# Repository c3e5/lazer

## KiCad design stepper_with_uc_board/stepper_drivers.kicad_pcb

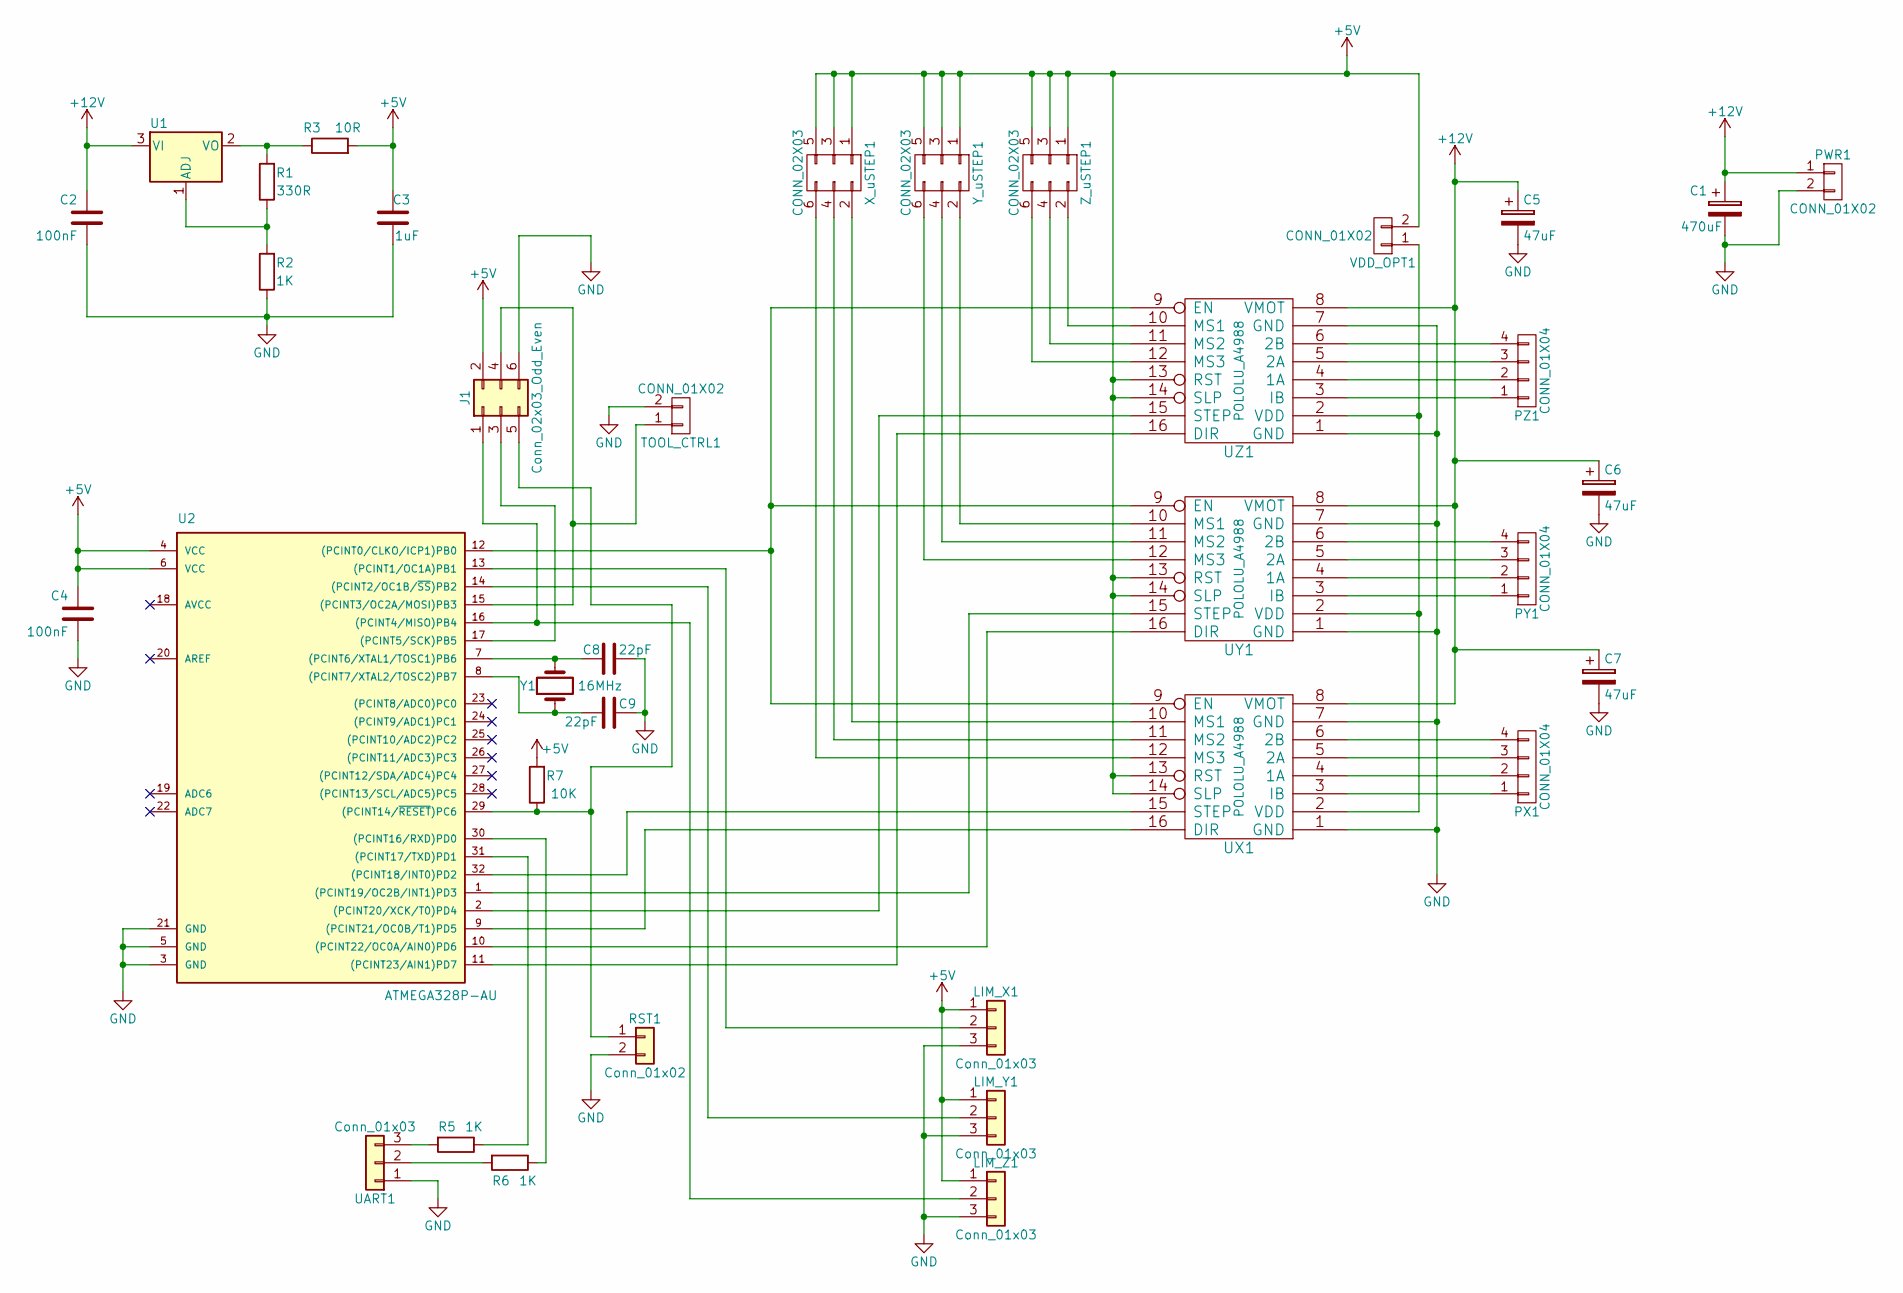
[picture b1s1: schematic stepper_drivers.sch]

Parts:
C1: 470uF; CP_Radial_D6.3mm_P2.50mm
C2, C4: 100nF; C_Rect_L4.0mm_W2.5mm_P2.50mm
C3: 1uF; CP_Radial_D4.0mm_P2.00mm
C5, C6, C7: 47uF; CP_Radial_D6.3mm_P2.50mm
C8, C9: 22pF; C_Rect_L4.0mm_W2.5mm_P2.50mm
J1: Conn_02x03_Odd_Even; Pin_Header_Straight_2x03_Pitch2.54mm
LIM_X1: Conn_01x03; Pin_Header_Straight_1x03_Pitch2.54mm
LIM_Y1: Conn_01x03; Pin_Header_Straight_1x03_Pitch2.54mm
LIM_Z1: Conn_01x03; Pin_Header_Straight_1x03_Pitch2.54mm
PWR1: CONN_01X02; TerminalBlock_Altech_AK300-2_P5.00mm
PX1: CONN_01X04; Socket_MOLEX-KK-RM2-54mm_Lock_4pin_straight
PY1: CONN_01X04; Socket_MOLEX-KK-RM2-54mm_Lock_4pin_straight
PZ1: CONN_01X04; Socket_MOLEX-KK-RM2-54mm_Lock_4pin_straight
R1: 330R; C_Rect_L4.0mm_W2.5mm_P2.50mm
R2, R5, R6: 1K; C_Rect_L4.0mm_W2.5mm_P2.50mm
R3: 10R; C_Rect_L4.0mm_W2.5mm_P2.50mm
R7: 10K; C_Rect_L4.0mm_W2.5mm_P2.50mm
RST1: Conn_01x02; TerminalBlock_bornier-2_P5.08mm
TOOL_CTRL1: CONN_01X02; Socket_MOLEX-KK-RM2-54mm_Lock_2pin_straight
U1: LM317_3PinPackage; SOT-223-3_TabPin2
U2: ATMEGA328P-AU; My_TQFP-32_7x7mm_Pitch0.8mm
UART1: Conn_01x03; Pin_Header_Straight_1x03_Pitch2.54mm
UX1: POLOLU_A4988; A4988
UY1: POLOLU_A4988; A4988
UZ1: POLOLU_A4988; A4988
VDD_OPT1: CONN_01X02; Pin_Header_Straight_1x02_Pitch2.54mm
X_uSTEP1: CONN_02X03; Pin_Header_Straight_2x03_Pitch2.54mm
Y1: 16MHz; Crystal_HC49-U_Vertical
Y_uSTEP1: CONN_02X03; Pin_Header_Straight_2x03_Pitch2.54mm
Z_uSTEP1: CONN_02X03; Pin_Header_Straight_2x03_Pitch2.54mm

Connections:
+5V: C3.2, C4.2, J1.2, LIM_X1.1, LIM_Y1.1, LIM_Z1.1, R3.2, R7.2, U2.4 (VCC), U2.6 (VCC), UX1.13 (RST), UX1.14 (SLP), UY1.13 (RST), UY1.14 (SLP), UZ1.13 (RST), UZ1.14 (SLP), VDD_OPT1.2, X_uSTEP1.1, X_uSTEP1.3, X_uSTEP1.5, Y_uSTEP1.1, Y_uSTEP1.3, Y_uSTEP1.5, Z_uSTEP1.1, Z_uSTEP1.3, Z_uSTEP1.5; also elsewhere on the board
+12V: C1.1, C2.2, C5.1, C6.1, C7.1, PWR1.1, U1.3 (VI), UX1.8 (VMOT), UY1.8 (VMOT), UZ1.8 (VMOT)
GND: C1.2, C2.1, C3.1, C4.1, C5.2, C6.2, C7.2, C8.1, C9.1, J1.6, LIM_X1.3, LIM_Y1.3, LIM_Z1.3, PWR1.2, R2.1, RST1.2, TOOL_CTRL1.2, U2.3 (GND), U2.5 (GND), U2.21 (GND), UART1.1, UX1.1 (GND), UX1.7 (GND), UY1.1 (GND), UY1.7 (GND), UZ1.1 (GND), UZ1.7 (GND); also elsewhere on the board
unnamed: C8.2, U2.7 ((PCINT6/XTAL1/TOSC1)PB6), Y1.2
unnamed: C9.2, U2.8 ((PCINT7/XTAL2/TOSC2)PB7), Y1.1
unnamed 5: J1.1, LIM_Z1.2, U2.16 ((PCINT4/MISO)PB4); also elsewhere on the board
unnamed 6: J1.3, U2.17 ((PCINT5/SCK)PB5); also elsewhere on the board
unnamed 7: J1.4, TOOL_CTRL1.1, U2.15 ((PCINT3/OC2A/MOSI)PB3); also elsewhere on the board
unnamed 8: J1.5, R7.1, RST1.1, U2.29 ((PCINT14/~RESET~)PC6); also elsewhere on the board
unnamed: LIM_X1.2, U2.13 ((PCINT1/OC1A)PB1)
unnamed 10: LIM_Y1.2, U2.14 ((PCINT2/OC1B/~SS~)PB2); also elsewhere on the board
unnamed: PX1.1, UX1.3 (IB)
unnamed: PX1.2, UX1.4 (1A)
unnamed: PX1.3, UX1.5 (2A)
unnamed: PX1.4, UX1.6 (2B)
unnamed: PY1.1, UY1.3 (IB)
unnamed: PY1.2, UY1.4 (1A)
unnamed: PY1.3, UY1.5 (2A)
unnamed: PY1.4, UY1.6 (2B)
unnamed: PZ1.1, UZ1.3 (IB)
unnamed: PZ1.2, UZ1.4 (1A)
unnamed: PZ1.3, UZ1.5 (2A)
unnamed: PZ1.4, UZ1.6 (2B)
unnamed: R1.1, R2.2, U1.1 (ADJ)
unnamed: R1.2, R3.1, U1.2 (VO)
unnamed: R5.1, U2.31 ((PCINT17/TXD)PD1)
unnamed: R5.2, UART1.3
unnamed: R6.1, U2.30 ((PCINT16/RXD)PD0)
unnamed: R6.2, UART1.2
unnamed: U2.1 ((PCINT19/OC2B/INT1)PD3), UY1.15 (STEP)
unnamed: U2.2 ((PCINT20/XCK/T0)PD4), UZ1.15 (STEP)
unnamed: U2.9 ((PCINT21/OC0B/T1)PD5), UX1.16 (DIR)
unnamed: U2.10 ((PCINT22/OC0A/AIN0)PD6), UY1.16 (DIR)
unnamed: U2.11 ((PCINT23/AIN1)PD7), UZ1.16 (DIR)
unnamed: U2.12 ((PCINT0/CLKO/ICP1)PB0), UX1.9 (EN), UY1.9 (EN), UZ1.9 (EN)
unnamed: U2.32 ((PCINT18/INT0)PD2), UX1.15 (STEP)
unnamed: UX1.2 (VDD), UY1.2 (VDD), UZ1.2 (VDD), VDD_OPT1.1
unnamed: UX1.10 (MS1), X_uSTEP1.2
unnamed: UX1.11 (MS2), X_uSTEP1.4
unnamed: UX1.12 (MS3), X_uSTEP1.6
unnamed: UY1.10 (MS1), Y_uSTEP1.2
unnamed: UY1.11 (MS2), Y_uSTEP1.4
unnamed: UY1.12 (MS3), Y_uSTEP1.6
unnamed: UZ1.10 (MS1), Z_uSTEP1.2
unnamed: UZ1.11 (MS2), Z_uSTEP1.4
unnamed: UZ1.12 (MS3), Z_uSTEP1.6

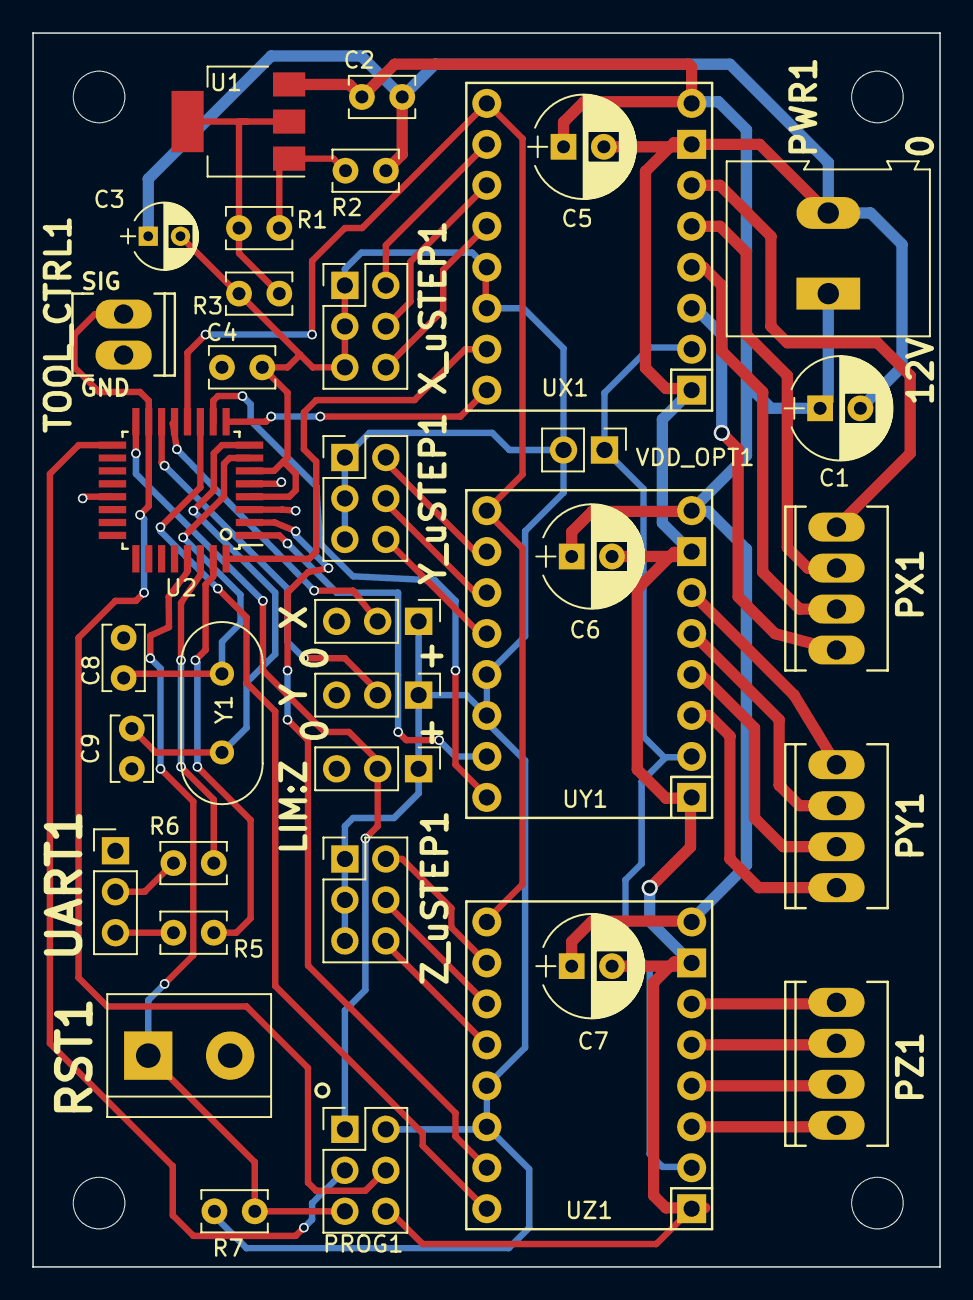
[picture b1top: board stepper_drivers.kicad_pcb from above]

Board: 2 copper layers, 56.2 x 76.5 mm, 36 parts (0 on the bottom side), 46 nets.

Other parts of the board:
LIM:Z   Y   X: Conn_01x03; Pin_Header_Straight_1x03_Pitch2.54mm
PROG1: Conn_02x03_Odd_Even; Pin_Header_Straight_2x03_Pitch2.54mm

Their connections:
+5V: LIM:Z Y X.1, PROG1.2; also elsewhere on the board
GND: LIM:Z Y X.3, PROG1.6; also elsewhere on the board
unnamed 5: PROG1.1; also elsewhere on the board
unnamed 6: PROG1.3; also elsewhere on the board
unnamed 7: PROG1.4; also elsewhere on the board
unnamed 8: PROG1.5; also elsewhere on the board
unnamed 10: LIM:Z Y X.2; also elsewhere on the board

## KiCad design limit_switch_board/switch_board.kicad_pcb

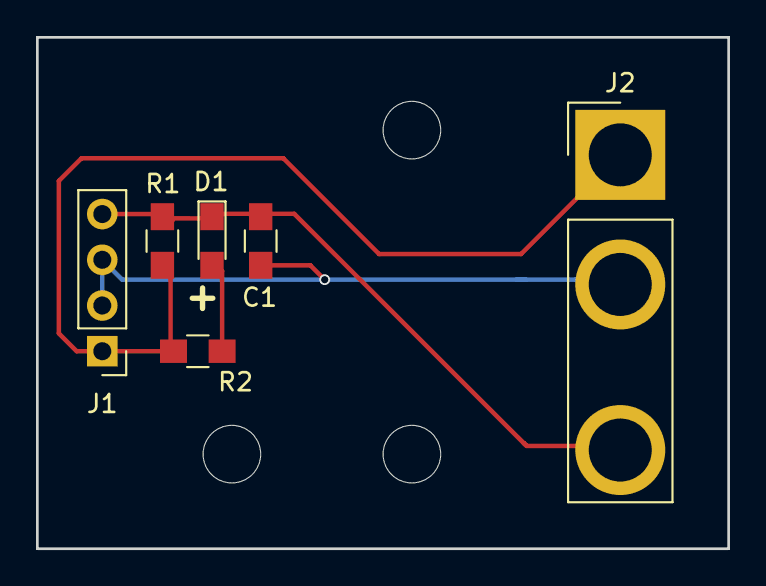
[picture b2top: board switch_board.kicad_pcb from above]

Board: 2 copper layers, 38.4 x 28.4 mm, 6 parts (0 on the bottom side), 4 nets.

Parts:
C1: 100nF; R_0805_HandSoldering
D1: LED; LED_0805_HandSoldering
J1: CONN_01X04; Pin_Header_Straight_1x04_Pitch2.54mm
J2: CONN_01X03; limit_switch_bomba
R1: 10K; R_0805_HandSoldering
R2: 1K; R_0805_HandSoldering

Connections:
+5V: J1.1, J2.2, R1.1, R2.1
GND: C1.2, J1.2, J1.3, J2.3
unnamed: C1.1, D1.1, J1.4, J2.1, R1.2
unnamed: D1.2, R2.2

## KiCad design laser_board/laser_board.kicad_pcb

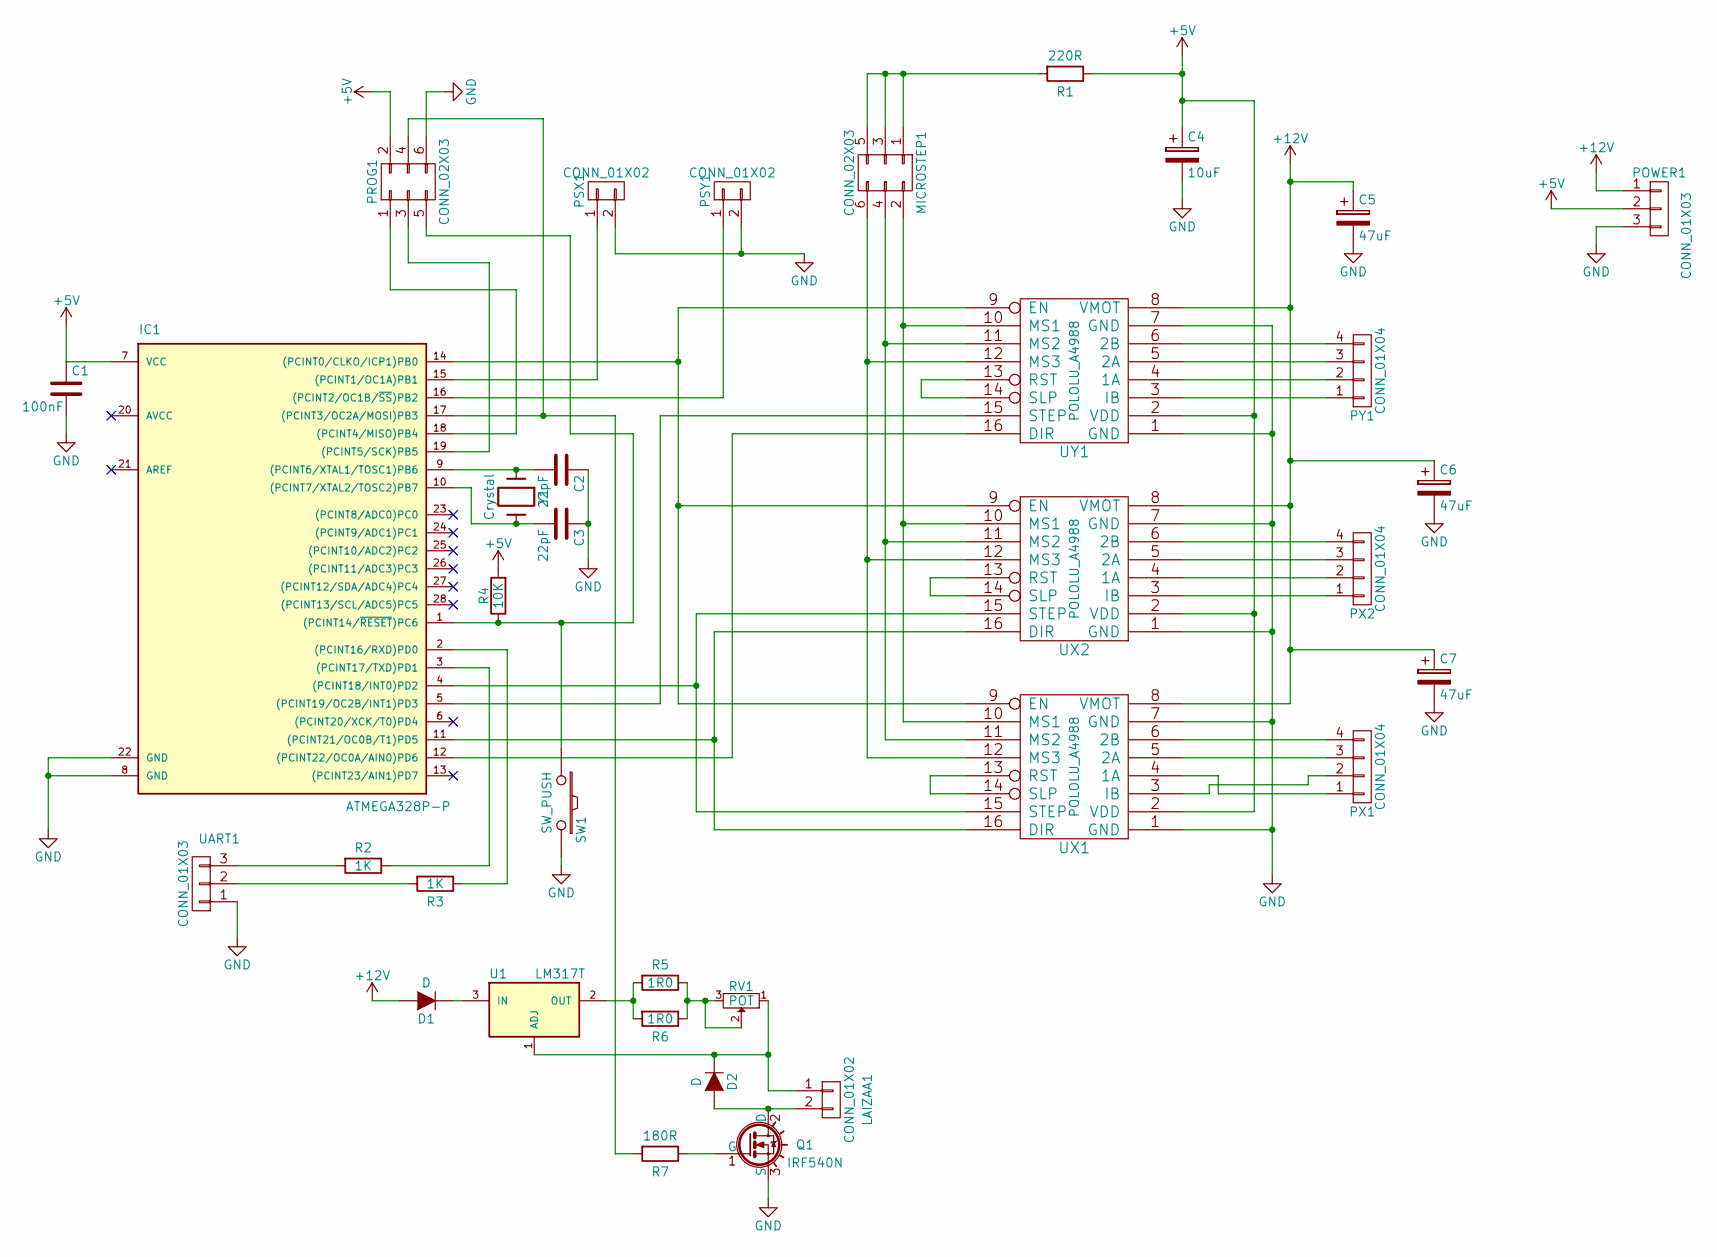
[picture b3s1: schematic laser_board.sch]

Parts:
C1: 100nF; C_Rect_L4_W2.5_P2.5
C2, C3: 22pF; C_Rect_L4_W2.5_P2.5
C4: 10uF; C_Radial_D5_L11_P2.5
C5, C6, C7: 47uF; C_Radial_D6.3_L11.2_P2.5
D1, D2: D; Diode_DO-41_SOD81_Vertical_KathodeUp
IC1: ATMEGA328P-P; DIP-28_W7.62mm
LAIZAA1: CONN_01X02; Socket_MOLEX-KK-RM2-54mm_Lock_2pin_straight
MICROSTEP1: CONN_02X03; Pin_Header_Straight_2x03
POWER1: CONN_01X03; Socket_MOLEX-KK-RM2-54mm_Lock_3pin_straight
PROG1: CONN_02X03; Pin_Header_Straight_2x03
PSX1: CONN_01X02; Socket_MOLEX-KK-RM2-54mm_Lock_2pin_straight
PSY1: CONN_01X02; Socket_MOLEX-KK-RM2-54mm_Lock_2pin_straight
PX1, PX2: CONN_01X04; Socket_MOLEX-KK-RM2-54mm_Lock_4pin_straight
PY1: CONN_01X04; Socket_MOLEX-KK-RM2-54mm_Lock_4pin_straight
Q1: IRF540N; TO-220
R1: 220R; C_Rect_L4_W2.5_P2.5
R2, R3: 1K; C_Rect_L4_W2.5_P2.5
R4: 10K; C_Rect_L4_W2.5_P2.5
R5, R6: 1R0; Resistor_Vertical_RM5mm
R7: 180R; C_Rect_L4_W2.5_P2.5
RV1: POT; Potentiometer_Bourns_3006P_Angular_ScrewFront
SW1: SW_PUSH; SIMPLE_SWITCH
U1: LM317T; TO-220
UART1: CONN_01X03; Pin_Header_Straight_1x03
UX1, UX2: POLOLU_A4988; A4988
UY1: POLOLU_A4988; A4988
Y1: Crystal; Crystal_HC49-U_Vertical

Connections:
+5V: C1.1, C4.1, IC1.7 (VCC), POWER1.2, PROG1.2, R1.1, R4.2, UX1.2 (VDD), UX2.2 (VDD), UY1.2 (VDD)
+12V: C5.1, C6.1, C7.1, D1.2 (A), POWER1.1, UX1.8 (VMOT), UX2.8 (VMOT), UY1.8 (VMOT)
GND: C1.2, C2.1, C3.1, C4.2, C5.2, C6.2, C7.2, IC1.8 (GND), IC1.22 (GND), POWER1.3, PROG1.6, PSX1.2, PSY1.2, Q1.3 (S), SW1.2, UART1.1, UX1.1 (GND), UX1.7 (GND), UX2.1 (GND), UX2.7 (GND), UY1.1 (GND), UY1.7 (GND)
unnamed: C2.2, IC1.9 ((PCINT6/XTAL1/TOSC1)PB6), Y1.1
unnamed: C3.2, IC1.10 ((PCINT7/XTAL2/TOSC2)PB7), Y1.2
unnamed: D1.1 (K), U1.3 (IN)
unnamed: D2.2 (A), LAIZAA1.2, Q1.2 (D)
unnamed: IC1.1 ((PCINT14/~RESET~)PC6), PROG1.5, R4.1, SW1.1
unnamed: IC1.2 ((PCINT16/RXD)PD0), R3.1
unnamed: IC1.3 ((PCINT17/TXD)PD1), R2.1
unnamed: IC1.4 ((PCINT18/INT0)PD2), UX1.15 (STEP), UX2.15 (STEP)
unnamed: IC1.5 ((PCINT19/OC2B/INT1)PD3), UY1.15 (STEP)
unnamed: IC1.11 ((PCINT21/OC0B/T1)PD5), UX1.16 (DIR), UX2.16 (DIR)
unnamed: IC1.12 ((PCINT22/OC0A/AIN0)PD6), UY1.16 (DIR)
unnamed: IC1.14 ((PCINT0/CLKO/ICP1)PB0), UX1.9 (EN), UX2.9 (EN), UY1.9 (EN)
unnamed: IC1.15 ((PCINT1/OC1A)PB1), PSX1.1
unnamed: IC1.16 ((PCINT2/OC1B/~SS~)PB2), PSY1.1
unnamed: IC1.17 ((PCINT3/OC2A/MOSI)PB3), PROG1.4, R7.2
unnamed: IC1.18 ((PCINT4/MISO)PB4), PROG1.1
unnamed: IC1.19 ((PCINT5/SCK)PB5), PROG1.3
unnamed: MICROSTEP1.1, MICROSTEP1.3, MICROSTEP1.5, R1.2
unnamed: MICROSTEP1.2, UX1.10 (MS1), UX2.10 (MS1), UY1.10 (MS1)
unnamed: MICROSTEP1.4, UX1.11 (MS2), UX2.11 (MS2), UY1.11 (MS2)
unnamed: MICROSTEP1.6, UX1.12 (MS3), UX2.12 (MS3), UY1.12 (MS3)
unnamed: PX1.1, UX1.4 (1A)
unnamed: PX1.2, UX1.3 (IB)
unnamed: PX1.3, UX1.5 (2A)
unnamed: PX1.4, UX1.6 (2B)
unnamed: PX2.1, UX2.3 (IB)
unnamed: PX2.2, UX2.4 (1A)
unnamed: PX2.3, UX2.5 (2A)
unnamed: PX2.4, UX2.6 (2B)
unnamed: PY1.1, UY1.3 (IB)
unnamed: PY1.2, UY1.4 (1A)
unnamed: PY1.3, UY1.5 (2A)
unnamed: PY1.4, UY1.6 (2B)
unnamed: Q1.1 (G), R7.1
unnamed: R2.2, UART1.3
unnamed: R3.2, UART1.2
unnamed: R5.2, R6.2, U1.2 (OUT)
unnamed: UX1.13 (RST), UX1.14 (SLP)
unnamed: UX2.13 (RST), UX2.14 (SLP)
unnamed: UY1.13 (RST), UY1.14 (SLP)

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
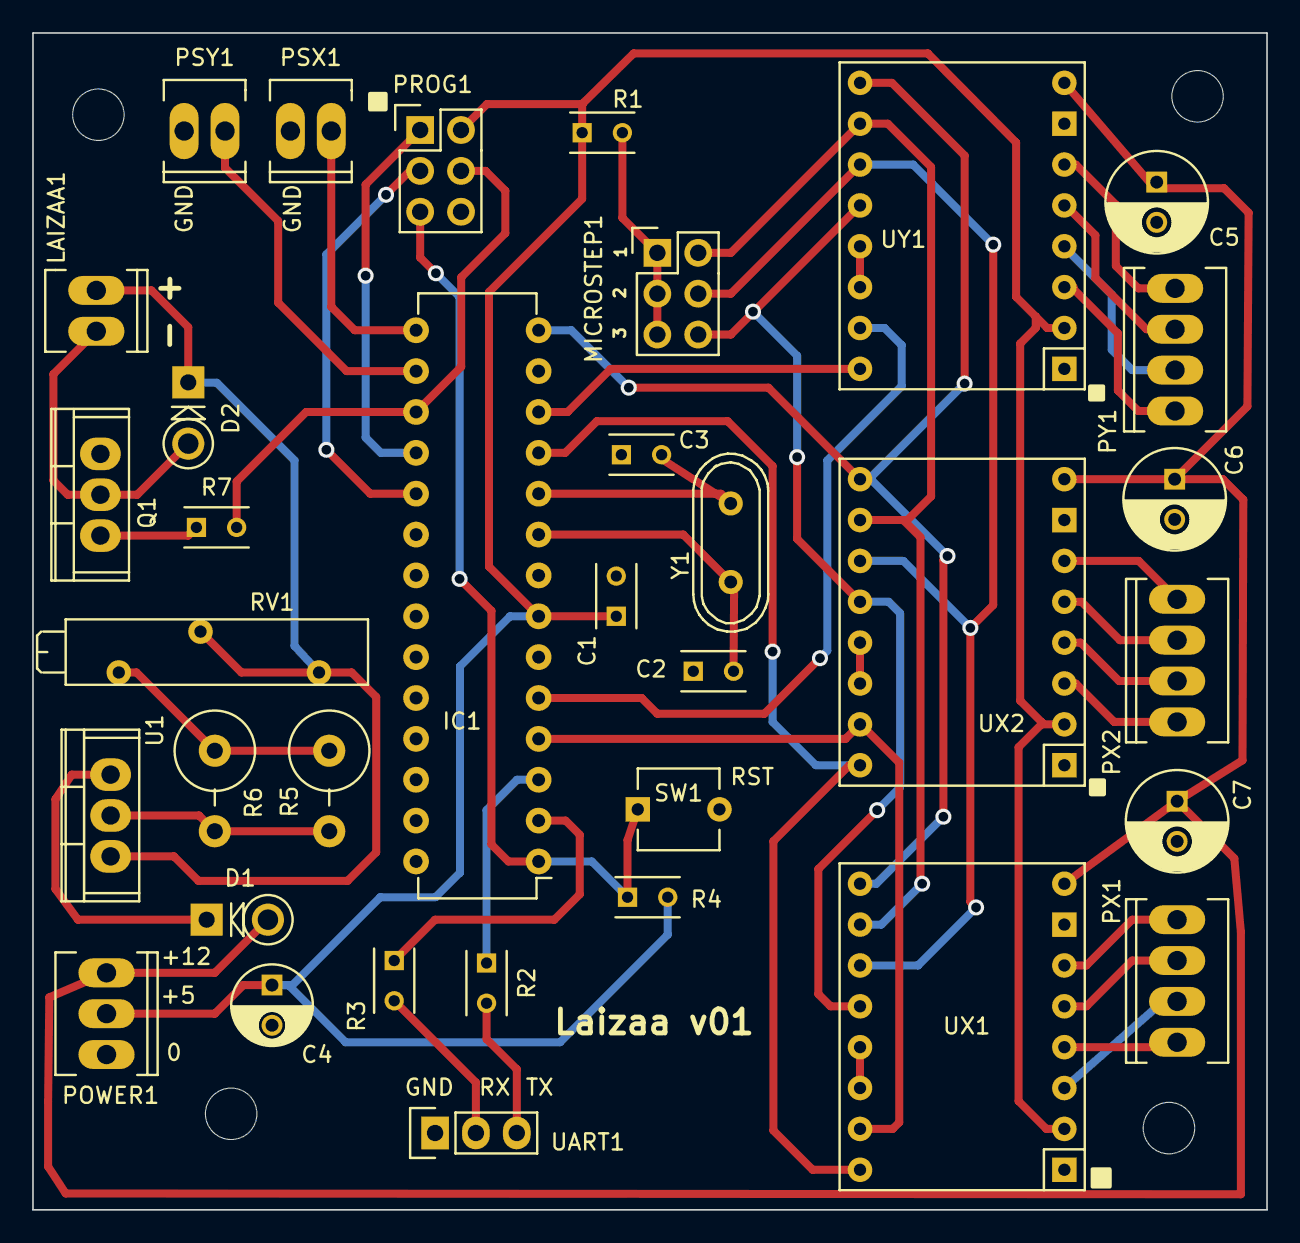
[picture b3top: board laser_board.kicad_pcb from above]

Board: 2 copper layers, 76.7 x 73.2 mm, 35 parts (0 on the bottom side), 45 nets.

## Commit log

2016-03-04 Adding some goodies to the laser board: 1. Laser driver 2. AVR programmer 3. Fixing a wrong wiring (arduino pin #2) 4. Crystal oscillator 5. Reset pin
2016-03-09 Schematics changes: 1. Adding UART 2. Adding a power connector 3. Adding some footprints 4. Adding a reset button 5. Adding some decoupling capacitors
2016-03-16 Adding a footprint for the A4988 board Assigning footprints Adding a PCB
2016-03-16 Fixing the board margins
2016-03-19 major PCB improvements
2016-03-19 laisaa board v01
2016-03-28 fix a pot route in the laser board
2016-07-15 Adding some G-Code examples
2016-07-30 more examples: kitty and c3e5
2016-08-06 bass icon sticker
2016-11-09 grbl config
2016-11-15 adding example: uri's portrait
2017-01-07 added ipad stand NGC
2017-01-09 added bluebell big logo files
2017-01-14 Generator to some star-form
2017-01-14 better comments and higher speed in oldschool.py
2017-01-14 renaming
2017-01-14 separate files for generic components
2017-01-16 updating Uri's SVG file
2017-01-16 adding Bet and Gimel
2017-01-17 adding a test for circle approximations
2017-01-27 gitignore
2017-04-09 Adding a first draft for a cardboard flower
2017-04-26 More cardboard flower + grbl/hifive init sequence
2017-05-04 Adding the CCC spaceship
2017-05-05 added spaceship base and 3d spaceship files
2017-05-05 cardboard flower improvements
2017-05-19 added hinge pattern generator and improved simplifier
2017-05-19 allow setting cut/passing feed in gcode generator
2017-05-19 support setting cut/passing feedrate from hinge command line
2017-06-02 rmz - script to remove the annoying Z axis operations
2017-06-19 Adding some more SVG files for cutting cardboard
2017-07-20 fixing init values for new super improved laizaa
2017-08-15 adding a board for limit switches
2017-08-15 adding a board for stepper motor drivers
2017-08-16 adding the stepper driver schematics in PDF
2017-09-07 minor board fixes: limit switches and stepper motors
2017-09-18 minor updates to motor drivers board
2017-10-20 Improved scripting - use vectors instead of tuples
2017-10-20 separate commands in grbl_init.txt
2017-10-20 Avoid going back in simplifier script
    Simplifier script now tries to avoid going back the same way it came
    from if possible.
    Also, added tunnels engraving for the resistor bender script.
2017-10-22 vectors can now have pre/post commands
2017-10-22 added path object to construct vectors by 'movement'
2017-10-22 moved do_square to Path
2017-10-23 ugsplatform does not allow soft limits w/o homing
2017-10-23 added some preparation gcode files
2017-10-23 moved init files into prep directory
2017-12-27 change hifive settings
2018-03-06 Adding some more art works
2018-03-06 hifive init params changed
2018-07-12 Fix a typo in the steppers board
2018-09-25 New PCB - still WIP - microcontroller with stepper drivers
2018-09-26 Additional text and some footprint fixes
2018-09-26 remove unnecessary files
2018-09-26 more minor fixes to the UC with stepper drivers board
